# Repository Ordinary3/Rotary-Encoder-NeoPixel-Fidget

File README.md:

**RELEASE NOTES: Version 2 🎉**
=====================================

**Summary**
-----------

Version 2 brings significant enhancements to the Arduino Neopixel Rotary Fidget Toy project, including:

* **Improved Structure**: Enhanced guide for easier navigation
* **Custom Modes**: Expanded functionality for a more engaging experience
* **Readability Updates**: Cleaner code for better understanding
* **Beginner-Friendly**: Simplified setup and operation for new users

**Important Notes**
-------------------

* **Compatibility**: If not using a custom PCB, consider sticking with Version 1 or adapting the Read Encoder from Version 1. some breakout  support Version 2.
* **Documentation**: Additional resources are pending and will be updated soon.
* **Licensing**: 
	+ **Commercial Use**: Prohibited without explicit permission.
	+ **Educational/Personal Use**: Permitted for learning and personal projects.

**Project Overview**
--------------------

### Arduino Neopixel Rotary Fidget Toy

* **Description**: Control a NeoPixel ring with various modes (color cycling, brightness adjustment, strobe effects) using a rotary encoder.
* **Design Tools**: KiCad v.6 (PCB design)
* **Future Plans**: Potential code rewrite using FastLED.h

**Required Components**
------------------------

1. **Microcontroller**: Arduino Nano or LGT8F328p
2. **Rotary Encoder**: EC11 (with or without breakout PCB)
3. **NeoPixel Ring**: 16 LEDs (you can use any version just edit #define NUM_PIXELS [n])
4. **Vibration Module**
5. **AWG 26 Wires**
6. **Button** (2) (For Mode switch and Reset)

**Optional Components**
-----------------------

1. **Slide Switch**
2. **Charging Module** (e.g., TP4056)
3. **Lipo Batt**
4. **Passive Buzzer** (Optional)

**Key Features**
----------------

* **Rotary Encoder Control**: Navigate modes and adjust settings
* **Color Modes**:
	+ Rainbow Cycle
	+ Rainbow Wave
	+ Rainbow Pulse
	+ Encoder-driven Color Selection
* **Brightness Adjustment**: Encoder-controlled
* **Strobe Effect**: Random strobe light activation
* **RGB Slider**: Smooth RGB color transitions
* **NEW Memory Game**: Identify LED patterns to win

**Breadboard Wiring Diagram**
-----------------------------

| Component | Arduino Pin |
| --- | --- |
| NeoPixel Data | 6 |
| Rotary Encoder A | 2 |
| Rotary Encoder B | 3 |
| Encoder Button | 4 |
| Mode Button | 7 |
| Vibration Motor | 5 |
| **Remember to connect Ground and Power accordingly.** |

**Acknowledgments**
------------------

* **Special Thanks to [pdp7](https://github.com/pdp7/rotary-encoder-breakout)**: This project is initially forked from their breakout board design.

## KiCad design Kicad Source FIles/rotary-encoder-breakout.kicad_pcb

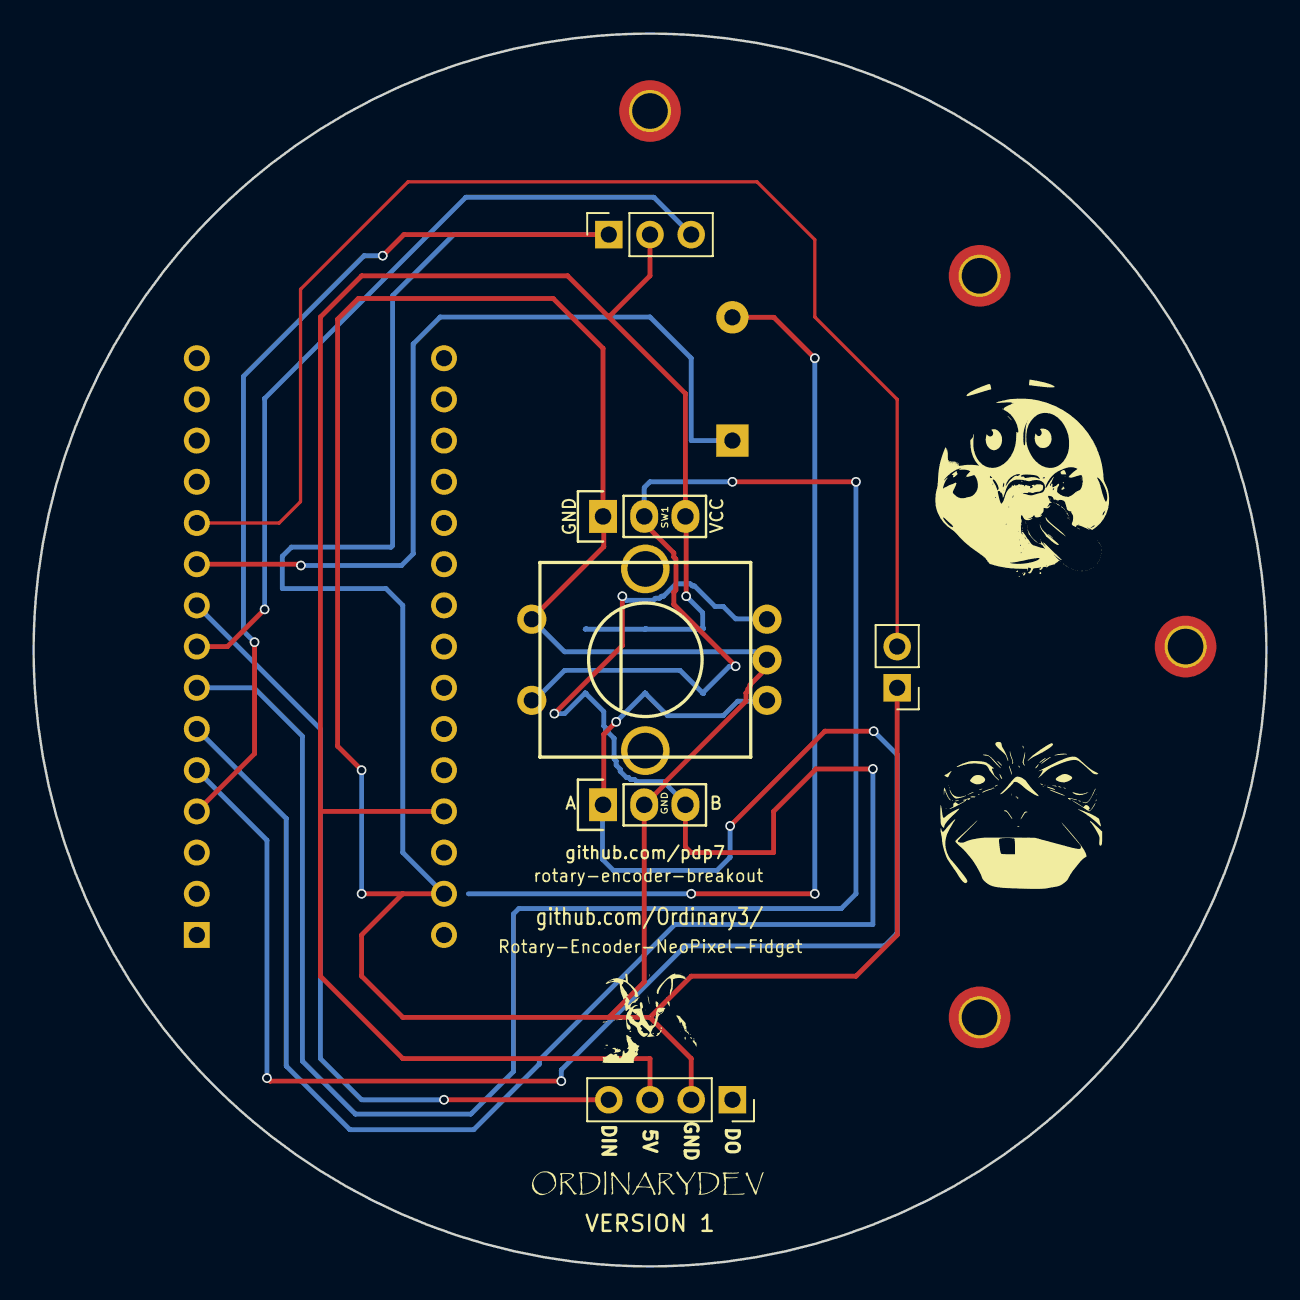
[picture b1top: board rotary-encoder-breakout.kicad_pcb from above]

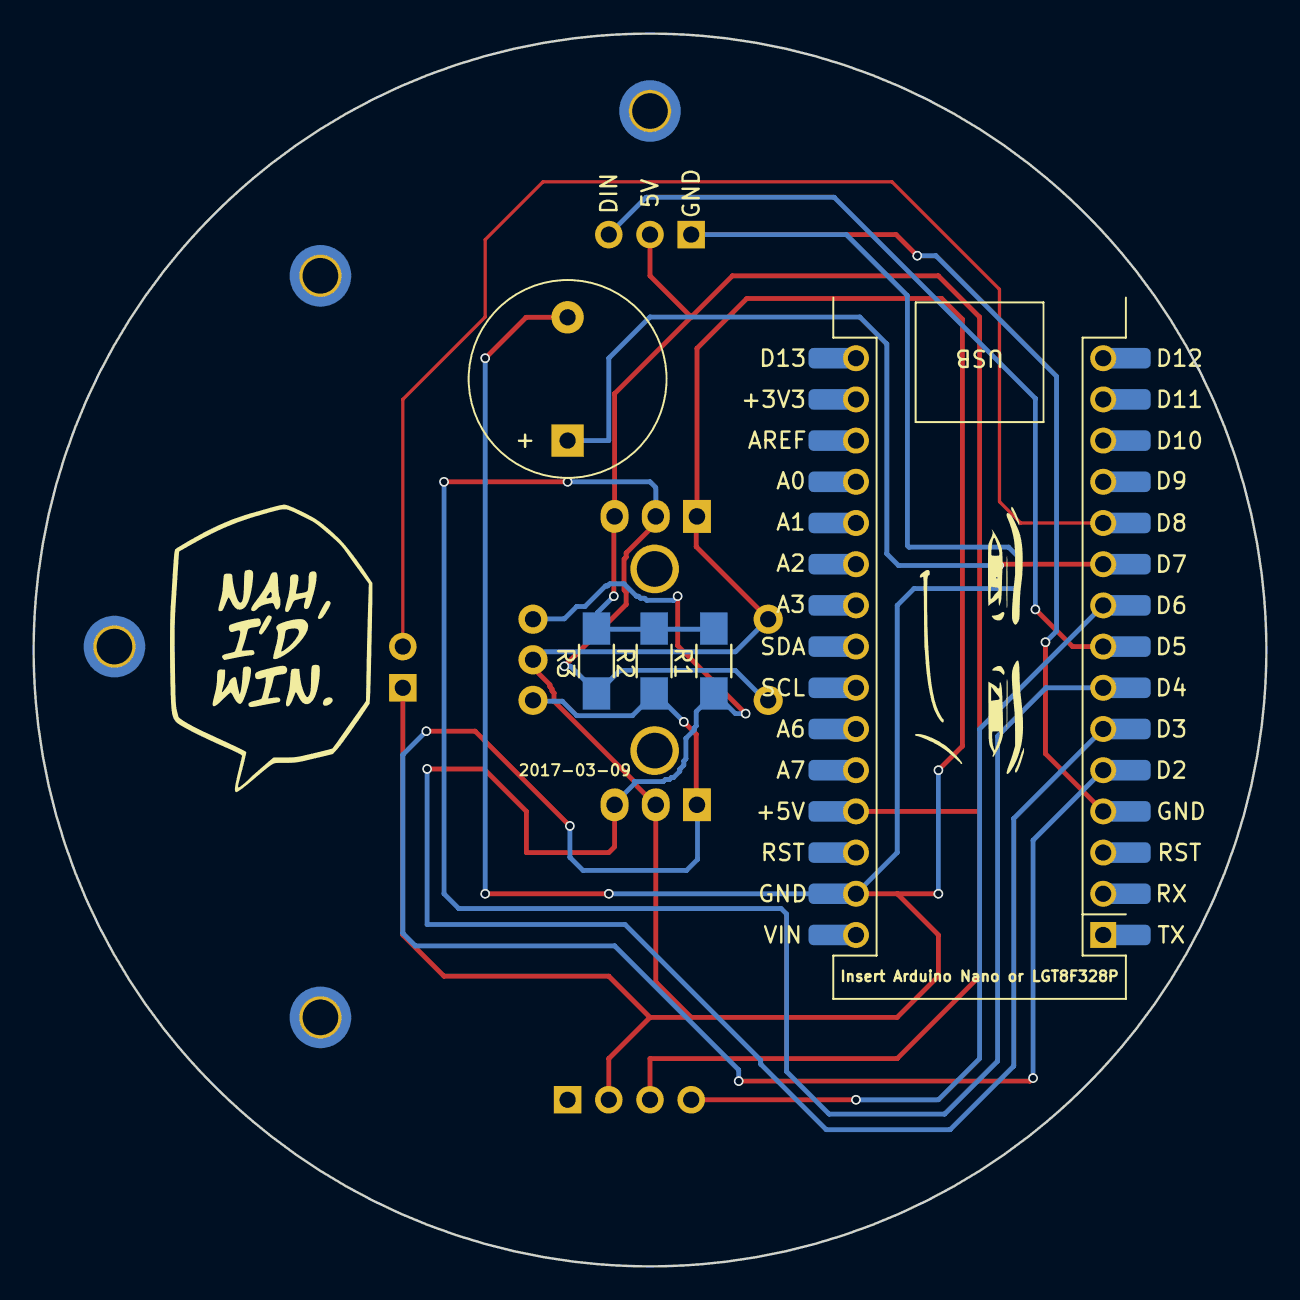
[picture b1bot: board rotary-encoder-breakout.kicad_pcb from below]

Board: 2 copper layers, 76.0 x 76.0 mm, 6 parts (3 on the bottom side), 5 nets.

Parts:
P1, P5: CONN_01X03; Pin_Header_Straight_1x03
R1, R2, R3: R; R_1206_HandSoldering
ROT1: ROTARY-ENCODER; SF-ROTARY-ENCODER

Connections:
/VCC: P1.3, R1.2, R2.2, R3.2
unnamed: P1.1, P5.2, ROT1.3, ROT1.5
unnamed: P1.2, R3.1, ROT1.1
unnamed: P5.1, R2.1, ROT1.2
unnamed: P5.3, R1.1, ROT1.4

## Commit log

2024-09-21 Update LICENSE
2024-09-22 Added PCB Files
2024-09-22 Added the ino files
2024-09-22 VERY IMPORTANT FIX
2024-09-22 Update README.md
    added more instructions
2024-09-22 Update README.md
    typo
2024-10-27 Brand new system
    Added Version 2 of the ledrotary code, If you are using a Rotary encoder with a breakout then use V1 if you are using the custom pcb then V2
2024-10-27 Version 2 Release 🎉
    Added some info on Version 2 might fix some stuff later :p
2024-10-27 Update V2.1 | QOL Update
    Made Easier to navigate the Repo and made the system more responsive for V2
    [V1 is also more responsive but the code is kinda unreadable]
2024-10-27 Small fix
2024-10-27 new license
2024-10-27 Version 2.1 Release 🎉
2024-10-27 No license
2024-10-27 Version 2.1 Release 🎉
    Fixed Readme
2024-10-27 Version 2.1 Release 🎉
    Fix
2024-10-28 V2.2 mode 8 hotfix
    Added a start anim to make it easier to look at
2024-10-28 V2.2 Readme rewrite again
    Better info
2024-10-28 LIcense
2024-10-28 V2.2.1 Visual QOL for game
    Made the correct leds that got selected show up
    Remove 599-602 to make the game harder
    gona add a difficulty selector
2024-11-03 v2.2 Hotfix
    Encoder button can be used for mode selecting
